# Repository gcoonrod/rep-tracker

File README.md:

# Rep Tracker

Weight lifting rep tracker device. This project is intended to be a learning exercise for digital circuit design and manufacture.

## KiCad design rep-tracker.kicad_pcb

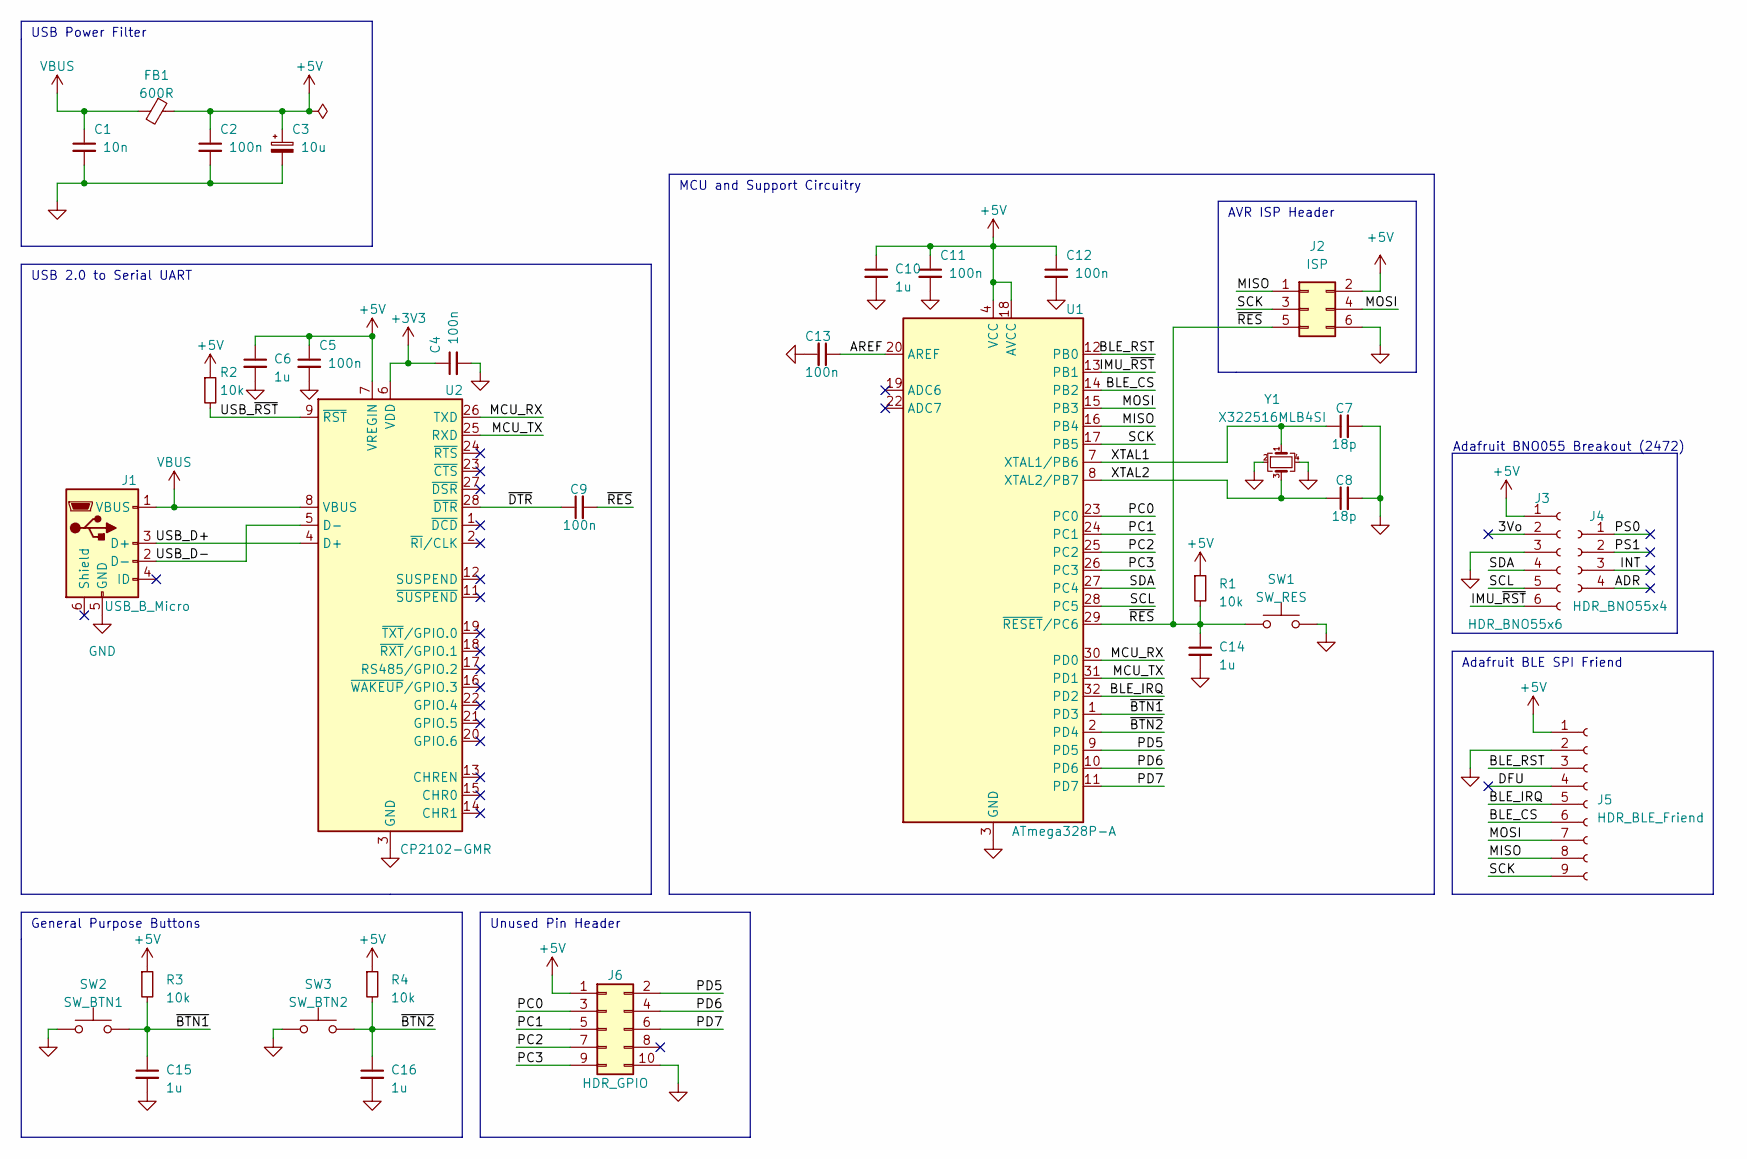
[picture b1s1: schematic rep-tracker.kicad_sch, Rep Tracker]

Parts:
C1: 10n; C_0402_1005Metric; Mfr Part CL05B103KB5NNNC
C2, C4, C5, C9, C11, C12, C13: 100n; C_0402_1005Metric; Mfr Part CL05B104KO5NNNC
C3: 10u; CP_EIA-3216-18_Kemet-A; Mfr Part TAJA106K016RNJ
C6, C10, C14, C15, C16: 1u; C_0402_1005Metric
C7, C8: 18p; C_0402_1005Metric; Mfr Part 0402CG180J500NT
FB1: 600R; C_0603_1608Metric; Mfr Part GZ1608D601TF
J1: USB_B_Micro; USB_Micro-B_Molex-105017-0001
J2: ISP; PinHeader_2x03_P2.54mm_Vertical
J3: HDR_BNO55x6; PinSocket_1x06_P2.54mm_Vertical
J4: HDR_BNO55x4; PinSocket_1x04_P2.54mm_Vertical
J5: HDR_BLE_Friend; PinSocket_1x09_P2.54mm_Vertical
J6: HDR_GPIO; PinSocket_2x05_P2.54mm_Vertical
R1, R2, R3, R4: 10k; R_0402_1005Metric
SW1: SW_RES; SW_Tactile_SPST_NO_Straight_CK_PTS636Sx25SMTRLFS
SW2: SW_BTN1; SW_Tactile_SPST_NO_Straight_CK_PTS636Sx25SMTRLFS
SW3: SW_BTN2; SW_Tactile_SPST_NO_Straight_CK_PTS636Sx25SMTRLFS
U1: ATmega328P-A; TQFP-32_7x7mm_P0.8mm
U2: CP2102-GMR; QFN-28-1EP_5x5mm_P0.5mm_EP3.35x3.35mm
Y1: X322516MLB4SI; Crystal_SMD_EuroQuartz_MT-4Pin_3.2x2.5mm; Mfr Part X322516MLB4SI

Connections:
+3V3: C4.1, U2.6 (VDD)
+5V: C2.1, C3.1, C5.1, C6.1, C10.1, C11.1, C12.1, FB1.1, J2.2, J3.1, J5.1, J6.1, R1.1, R2.1, R3.1, R4.1, U1.4 (VCC), U1.6 (VCC), U1.18 (AVCC), U2.7 (VREGIN)
/3Vo: J3.2
/ADR: J4.4
/AREF: C13.1, U1.20 (AREF)
/BLE_CS: J5.6, U1.14 (PB2)
/BLE_IRQ: J5.5, U1.32 (PD2)
/BLE_RST: J5.3, U1.12 (PB0)
/DFU: J5.4
/IMU_~RST: J3.6, U1.13 (PB1)
/INT: J4.3
/MCU_RX: U1.30 (PD0), U2.26 (TXD)
/MCU_TX: U1.31 (PD1), U2.25 (RXD)
/MISO: J2.1, J5.8, U1.16 (PB4)
/MOSI: J2.4, J5.7, U1.15 (PB3)
/PC0: J6.3, U1.23 (PC0)
/PC1: J6.5, U1.24 (PC1)
/PC2: J6.7, U1.25 (PC2)
/PC3: J6.9, U1.26 (PC3)
/PD5: J6.2, U1.9 (PD5)
/PD6: J6.4, U1.10 (PD6)
/PD7: J6.6, U1.11 (PD7)
/PS0: J4.1
/PS1: J4.2
/SCK: J2.3, J5.9, U1.17 (PB5)
/SCL: J3.5, U1.28 (PC5)
/SDA: J3.4, U1.27 (PC4)
/USB_D+: J1.3 (D+), U2.4 (D+)
/USB_D-: J1.2 (D-), U2.5 (D-)
/USB_~RST: R2.2, U2.9 (~RST)
/XTAL1: C7.1, U1.7 (XTAL1/PB6), Y1.1
/XTAL2: C8.1, U1.8 (XTAL2/PB7), Y1.3
/~BTN1: C15.1, R3.2, SW2.2, U1.1 (PD3)
/~BTN2: C16.1, R4.2, SW3.2, U1.2 (PD4)
/~DTR: C9.1, U2.28 (~DTR)
/~RES: C9.2, C14.1, J2.5, R1.2, SW1.1, U1.29 (~RESET/PC6)
GND: C1.2, C2.2, C3.2, C4.2, C5.2, C6.2, C7.2, C8.2, C10.2, C11.2, C12.2, C13.2, C14.2, C15.2, C16.2, J1.5 (GND), J2.6, J3.3, J5.2, J6.10, SW1.2, SW2.1, SW3.1, U1.3 (GND), U1.5 (GND), U1.21 (GND), U2.3 (GND), U2.29 (GND), Y1.2, Y1.4
VBUS: C1.1, FB1.2, J1.1 (VBUS), U2.8 (VBUS)

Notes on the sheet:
AVR ISP Header
USB 2.0 to Serial UART
General Purpose Buttons
MCU and Support Circuitry
Unused Pin Header
Adafruit BNO055 Breakout (2472)
USB Power Filter
Adafruit BLE SPI Friend

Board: 4 copper layers, 33 parts (0 on the bottom side), 32 nets, no tracks yet.

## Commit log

2023-06-03 move readme
